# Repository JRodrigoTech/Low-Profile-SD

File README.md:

# Low-Profile microSD card adapter for Raspberry Pi

Make your Pi a little slimmer with this microSD card adapter board. It slides in where the SD card goes but is half the length. Pop in a microSD card for a sleeker machine. The microSD card holder is a push-push type so you can push on the edge that sticks out to remove the card when necessary.

Depending on the case from various manufacturers, the microSD card adapter may not easily slide in and out or may need modifications to the PCB or actual case. The microSD card adapter is meant for a stand alone board. We will compile a list of compatible cases in the future.

# License

Released under [Creative Commons Attribution and Share Alike License](http://creativecommons.org/licenses/by-sa/4.0/) by [J.Rodrigo](http://www.jrodrigo.net)

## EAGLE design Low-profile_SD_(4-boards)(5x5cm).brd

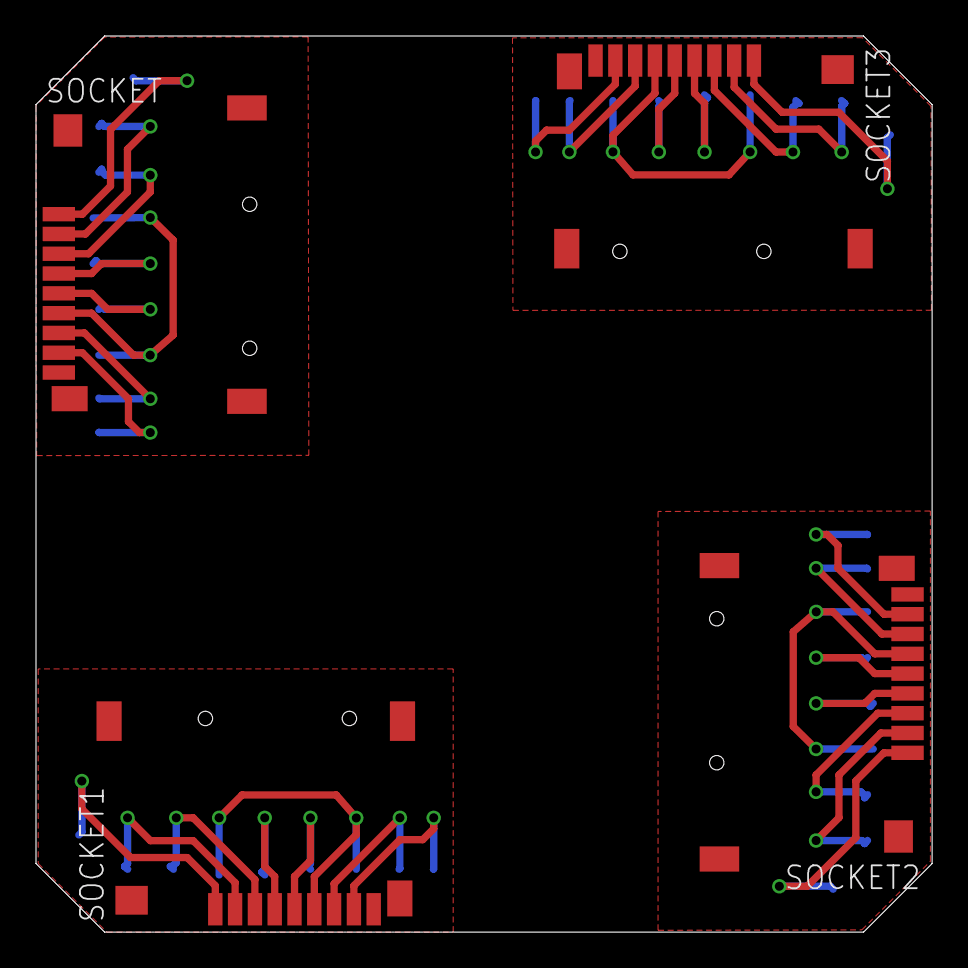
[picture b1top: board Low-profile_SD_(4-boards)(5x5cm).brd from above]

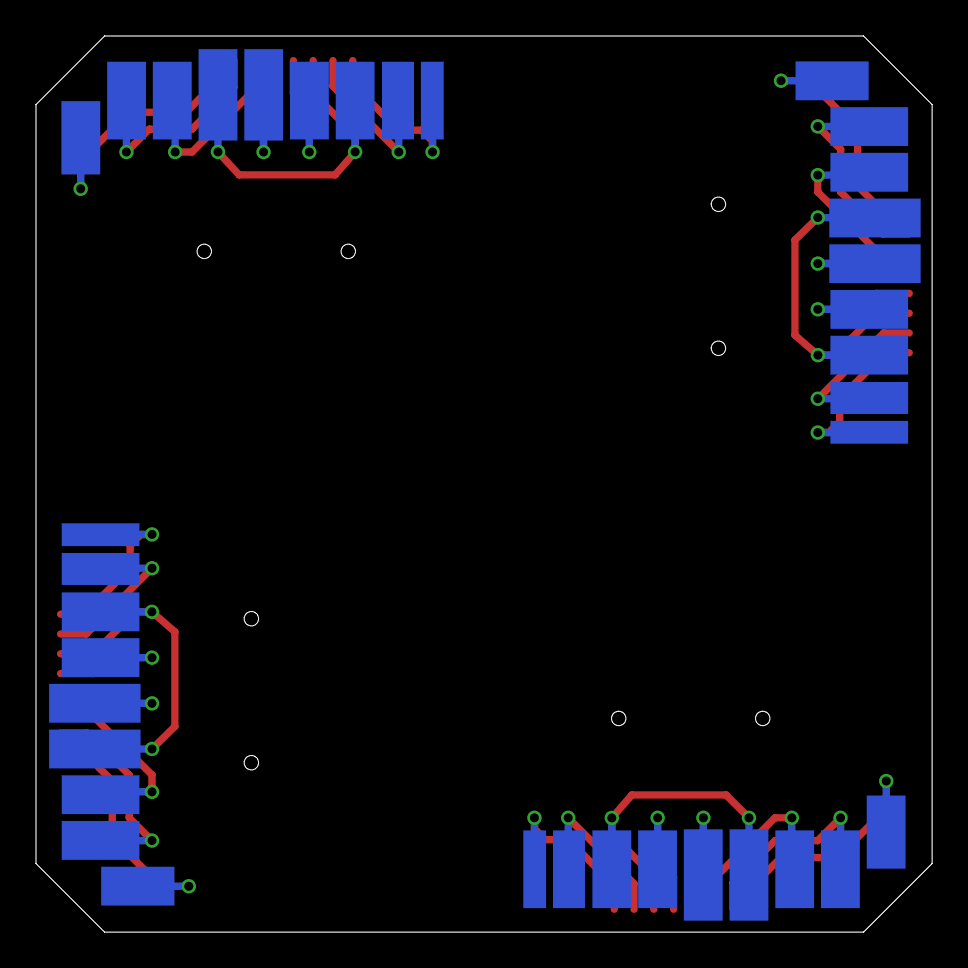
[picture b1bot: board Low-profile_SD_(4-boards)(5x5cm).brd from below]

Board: 2 copper layers, 49.8 x 49.8 mm, 8 parts (4 on the bottom side), 36 nets.

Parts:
SD-PCB, SD-PCB1, SD-PCB2, SD-PCB3: SD_CARD_PADS; SD_PADS
SOCKET, SOCKET1, SOCKET2, SOCKET3: MICROSD; MICROSD_PP

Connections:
GND: SOCKET.GND@1, SOCKET.GND@2, SOCKET.GND@3, SOCKET.GND@4
GND1: SOCKET1.GND@1, SOCKET1.GND@2, SOCKET1.GND@3, SOCKET1.GND@4
GND2: SOCKET2.GND@1, SOCKET2.GND@2, SOCKET2.GND@3, SOCKET2.GND@4
GND3: SOCKET3.GND@1, SOCKET3.GND@2, SOCKET3.GND@3, SOCKET3.GND@4
unnamed: SD-PCB.DAT3, SOCKET.2
unnamed: SD-PCB.CMD, SOCKET.3
unnamed: SD-PCB.VDD, SOCKET.4
unnamed: SD-PCB.CLK, SOCKET.5
unnamed: SD-PCB.VSS1, SD-PCB.VSS2, SOCKET.6
unnamed: SD-PCB.DAT0, SOCKET.7
unnamed: SD-PCB.DAT1, SOCKET.8
unnamed: SD-PCB.DAT2, SOCKET.1
unnamed: SD-PCB1.DAT3, SOCKET1.2
unnamed: SD-PCB1.CMD, SOCKET1.3
unnamed: SD-PCB1.VDD, SOCKET1.4
unnamed: SD-PCB1.CLK, SOCKET1.5
unnamed: SD-PCB1.VSS1, SD-PCB1.VSS2, SOCKET1.6
unnamed: SD-PCB1.DAT0, SOCKET1.7
unnamed: SD-PCB1.DAT1, SOCKET1.8
unnamed: SD-PCB1.DAT2, SOCKET1.1
unnamed: SD-PCB2.DAT3, SOCKET2.2
unnamed: SD-PCB2.CMD, SOCKET2.3
unnamed: SD-PCB2.VDD, SOCKET2.4
unnamed: SD-PCB2.CLK, SOCKET2.5
unnamed: SD-PCB2.VSS1, SD-PCB2.VSS2, SOCKET2.6
unnamed: SD-PCB2.DAT0, SOCKET2.7
unnamed: SD-PCB2.DAT1, SOCKET2.8
unnamed: SD-PCB2.DAT2, SOCKET2.1
unnamed: SD-PCB3.DAT3, SOCKET3.2
unnamed: SD-PCB3.CMD, SOCKET3.3
unnamed: SD-PCB3.VDD, SOCKET3.4
unnamed: SD-PCB3.CLK, SOCKET3.5
unnamed: SD-PCB3.VSS1, SD-PCB3.VSS2, SOCKET3.6
unnamed: SD-PCB3.DAT0, SOCKET3.7
unnamed: SD-PCB3.DAT1, SOCKET3.8
unnamed: SD-PCB3.DAT2, SOCKET3.1

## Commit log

2015-02-23 Updated
    Added licence and description.
2015-02-23 Released
2015-02-23 Updated
    Updated license link
